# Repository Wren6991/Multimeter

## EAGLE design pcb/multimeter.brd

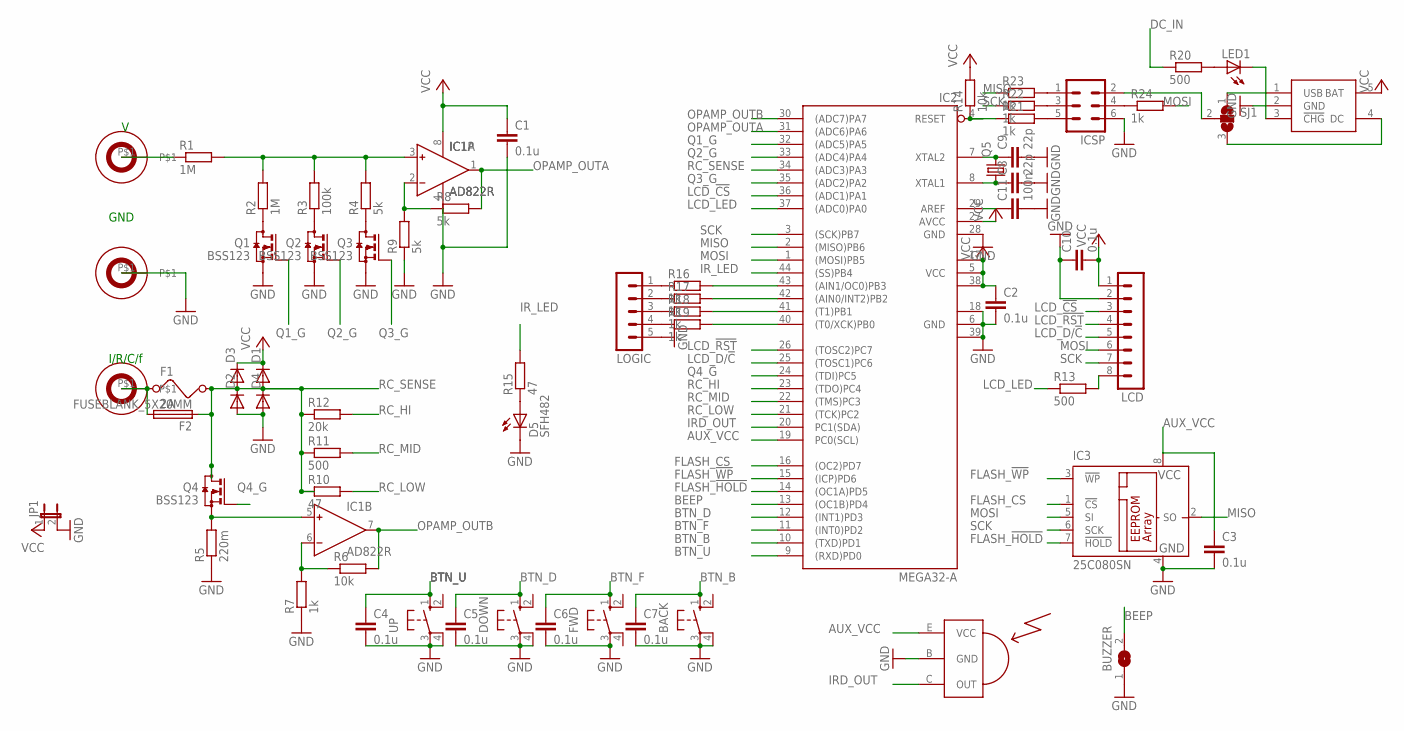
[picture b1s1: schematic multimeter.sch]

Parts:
BACK: 10-XX; B3F-10XX
BUZZER: SJW
C1, C2, C3, C4, C5, C6, C7, C10: 0.1u; C0805
C8, C9: 22p; C0603
C11: 100n; C0805
D1, D2, D3, D4: DIODE-SOD123; SOD123
D5: SFH482
DOWN: 10-XX; B3F-10XX
F1: 2A; R1206
F2: FUSEBLANK_5X20MM; FUSE_HOLDER_5X20MM
FWD: 10-XX; B3F-10XX
IC1: AD822R; SO8
IC2: MEGA32-A; TQFP44
IC3: 25C080SN; SO-08
ICSP: MA03-2
JP1: JP1E; JP1
LCD: MA08-1
LED1: LEDSML0805; SML0805
LOGIC: MA05-1
N$36: BINDINGPOST4MMPCB; BINDINGPOSTPCB
Q1, Q2, Q3, Q4: BSS123; SOT23
Q5: CRYSTALHC49UP; HC49UP
R1: 1M; 0207/12
R2: 1M; R0805
R3: 100k; R0805
R4, R8, R9: 5k; R0805
R5: 220m; R1206
R6, R14: 10k; R0805
R7, R16, R17, R18, R19, R21, R22, R23, R24: 1k; R0805
R10, R15: 47; R0805
R11, R13, R20: 500; R0805
R12: 20k; R0805
SJ1: SJ2W; SJ_2
U$1, U$2: BINDINGPOST4MMPCB; BINDINGPOSTPCB
U$3: IRDETECTOR; TO92-EBC
U$4: LITHIUMCHARGER; SOT23-5L
UP: 10-XX; B3F-10XX

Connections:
AUX_VCC: C3.1, IC2.19 (PC0(SCL)), IC3.8 (VCC), U$3.E (VCC)
BEEP: BUZZER.2, IC2.13 ((OC1B)PD4)
BTN_B: BACK.1 (S), C7.1, IC2.10 ((TXD)PD1)
BTN_D: C5.1, DOWN.1 (S), IC2.12 ((INT1)PD3)
BTN_F: C6.1, FWD.1 (S), IC2.11 ((INT0)PD2)
BTN_U: C4.1, IC2.9 ((RXD)PD0), UP.1 (S)
DC_IN: ICSP.2, R20.1, SJ1.2
FLASH_!HOLD: IC2.14 ((OC1A)PD5), IC3.7 (!HOLD)
FLASH_!WP: IC2.15 ((ICP)PD6), IC3.3 (!WP)
FLASH_CS: IC2.16 ((OC2)PD7), IC3.1 (!CS)
GND: BACK.3, BACK.4 (P1), BUZZER.1, C1.2, C2.2, C3.2, C4.2, C5.2, C6.2, C7.2, C8.2, C9.2, C10.1, C11.2, D2.A, D4.A, D5.K (C), DOWN.3, DOWN.4 (P1), FWD.3, IC1.4 (V-), IC2.6 (GND), IC2.18 (GND1), IC2.28 (GND), IC2.39 (GND2), IC3.4 (GND), ICSP.6, JP1.2, LCD.2, LOGIC.5, Q1.2 (S), Q2.2 (S), Q3.2 (S), R5.1, R7.1, R9.1, U$2.P$1, U$3.B (GND), U$4.2 (GND), UP.3, UP.4 (P1)
IRD_OUT: IC2.20 (PC1(SDA)), U$3.C (OUT)
IR_LED: IC2.44 ((SS)PB4), R15.2
LCD_!CS: IC2.36 ((ADC1)PA1), LCD.3
LCD_!RST: IC2.26 ((TOSC2)PC7), LCD.4
LCD_D/!C: IC2.25 ((TOSC1)PC6), LCD.5
LCD_LED: IC2.37 ((ADC0)PA0), R13.1
MISO: IC2.2 ((MISO)PB6), IC3.2 (SO), R23.1
MOSI: IC2.1 ((MOSI)PB5), IC3.5 (SI), LCD.6, R24.2
unnamed: D5.A, R15.1
unnamed: Q2.3 (D), R3.1
unnamed: LOGIC.1, R16.1
unnamed: IC1.3 (IN+), R1.2, R2.2, R3.2, R4.2
unnamed: IC1.5 (IN+), Q4.2 (S), R5.2
unnamed: LOGIC.2, R17.1
unnamed: IC1.6 (IN-), R6.1, R7.2
unnamed: LOGIC.3, R18.1
unnamed: IC1.2 (IN-), R8.1, R9.2
unnamed: LOGIC.4, R19.1
unnamed: IC2.43 ((AIN1/OC0)PB3), R16.2
unnamed: ICSP.4, R24.1
unnamed: IC2.42 ((AIN0/INT2)PB2), R17.2
unnamed: IC2.41 ((T1)PB1), R18.2
unnamed: IC2.40 ((T0/XCK)PB0), R19.2
unnamed: C9.1, IC2.7 (XTAL2), Q5.2
unnamed: R1.1, U$1.P$1
unnamed: C8.1, IC2.8 (XTAL1), Q5.1
unnamed: SJ1.3, U$4.4 (DC)
unnamed: IC2.4 (RESET), R14.1, R21.1
unnamed: SJ1.1, U$4.1 (USB)
unnamed: LED1.A, R20.2
unnamed: LED1.C, U$4.3 (!CHG)
unnamed: ICSP.5, R21.2
unnamed: ICSP.3, R22.2
unnamed: ICSP.1, R23.2
unnamed: C11.1, IC2.29 (AREF)
unnamed: LCD.8, R13.2
unnamed: F1.1, F2.2, N$36.P$1
unnamed: Q1.3 (D), R2.1
unnamed: Q3.3 (D), R4.1
OPAMP_OUTA: IC1.1 (OUT), IC2.31 ((ADC6)PA6), R8.2
OPAMP_OUTB: IC1.7 (OUT), IC2.30 ((ADC7)PA7), R6.2
Q1_G: IC2.32 ((ADC5)PA5), Q1.1 (G)
Q2_G: IC2.33 ((ADC4)PA4), Q2.1 (G)
Q3_G: IC2.35 ((ADC2)PA2), Q3.1 (G)
Q4_G: IC2.24 ((TDI)PC5), Q4.1 (G)
RC_HI: IC2.23 ((TDO)PC4), R12.2
RC_LOW: IC2.21 ((TCK)PC2), R10.2
RC_MID: IC2.22 ((TMS)PC3), R11.2
RC_SENSE: D1.A, D2.C, D3.A, D4.C, F1.2, F2.1, IC2.34 ((ADC3)PA3), Q4.3 (D), R10.1, R11.1, R12.1
SCK: IC2.3 ((SCK)PB7), IC3.6 (SCK), LCD.7, R22.1
VCC: C1.1, C2.1, C10.2, D1.C, D3.C, IC1.8 (V+), IC2.5 (VCC), IC2.17 (VCC1), IC2.27 (AVCC), IC2.38 (VCC2), JP1.1, LCD.1, R14.2, U$4.5 (BAT)

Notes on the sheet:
GND
I/R/C/f

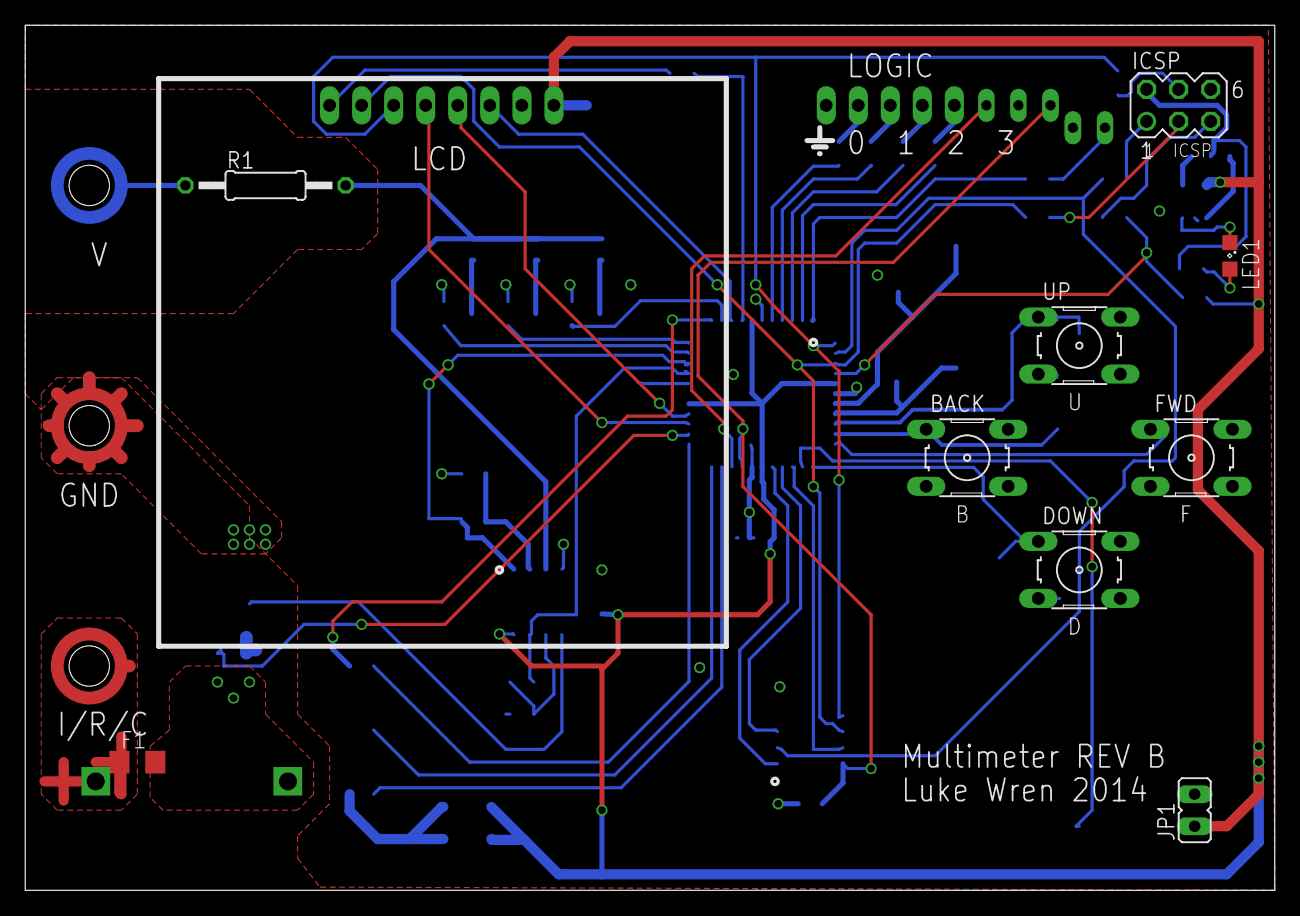
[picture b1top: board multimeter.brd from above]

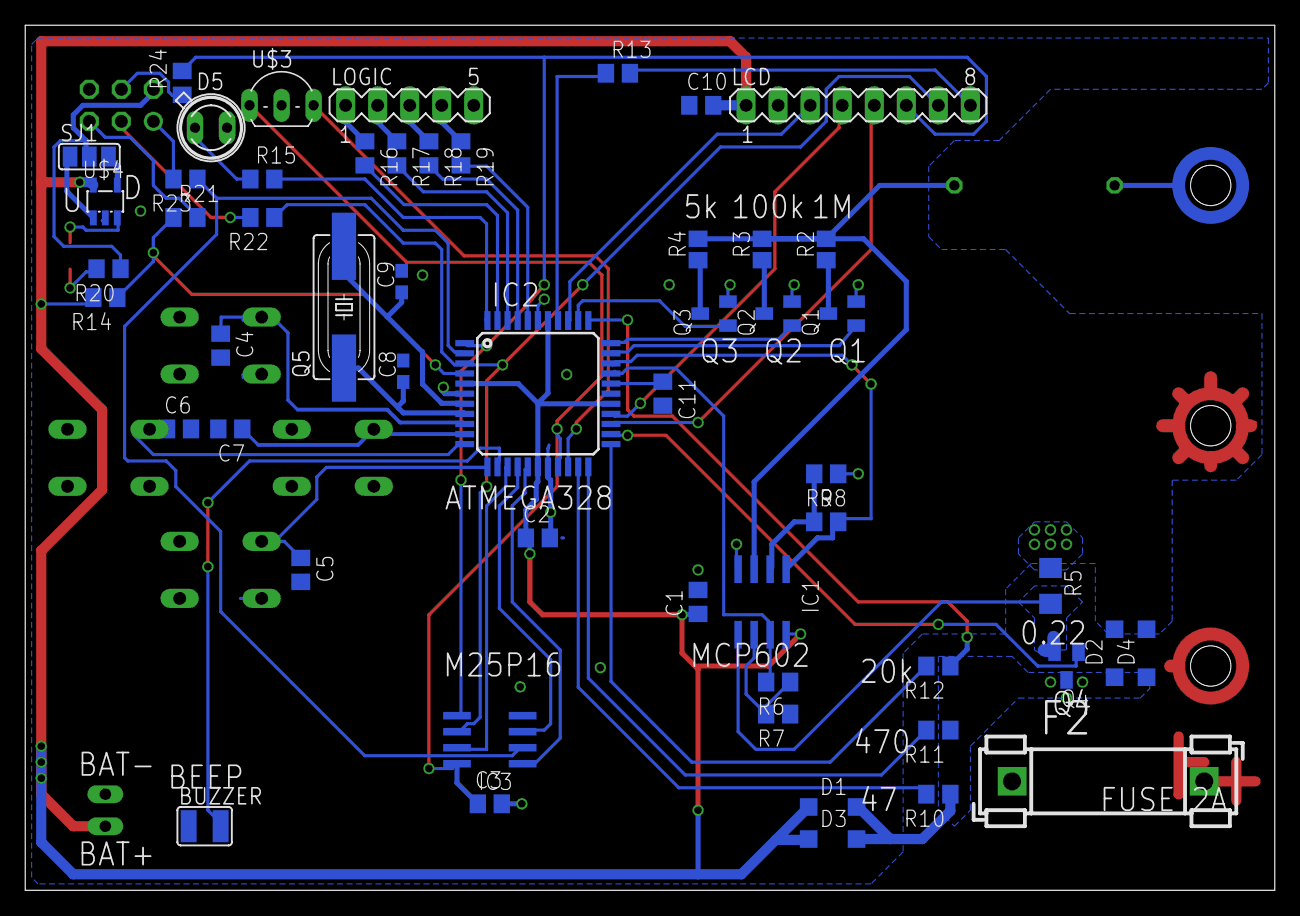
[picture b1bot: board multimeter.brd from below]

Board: 2 copper layers, 99.1 x 68.6 mm, 66 parts (55 on the bottom side), 62 nets.

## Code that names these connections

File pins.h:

#ifndef _PINS_H_
#define _PINS_H_

#define PORT_VATTEN PORTA
#define DDR_VATTEN DDRA
#define VATTEN_1M 0x20
#define VATTEN_100k 0x10
#define VATTEN_5k 0x04
#define VATTEN_ALL (VATTEN_1M | VATTEN_100k | VATTEN_5k)

#define DDR_IGATE DDRC
#define PORT_IGATE PORTC
#define IGATE 0x20
#define CURRENT_ON true
#define CURRENT_OFF false

#define PORT_RC PORTC
#define DDR_RC DDRC
#define RC_HI 0x10
#define RC_MID 0x08
#define RC_LOW 0x04

#define PORT_RCSENSE PORTA
#define DDR_RCSENSE DDRA
#define PIN_RCSENSE PINA
#define RC_SENSE 0x08

#define VIN_V 6
#define VIN_I 7
#define VIN_RC 3
#define VIN_BANDGAP 0x1e

#endif // _PINS_H_

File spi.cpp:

#include "spi.h"

#define LCD_CS 0x02
#define PORT_LCD_CS PORTA
#define DDR_LCD_CS DDRA
#define FLASH_CS 0x80
#define FLASH_WP 0x40
#define FLASH_HOLD 0x20
#define PORT_FLASH_CS PORTD
#define DDR_FLASH_CS DDRD

#define PORT_SPI PORTB
#define DDR_SPI DDRB
#define SPI_MOSI 0x20
#define SPI_MISO 0x40
#define SPI_SCK 0x80
#define SPI_SS 0x10
#define SPI_ALL (SPI_MOSI | SPI_MISO | SPI_SCK | SPI_SS)

void spi_init()
{
    spi_deassert();
    DDR_SPI = (DDR_SPI & ~SPI_ALL) | (SPI_MOSI | SPI_SCK | SPI_SS);
    SPCR0 = 0x50;    // no interrupt, SPI enabled, MSB first, master, divide clock by four (on top of four phases)
    SPSR0 = 0x01;    // SPI2X enabled (gives effective SPI clock of FCPU/8 = 1MHz)
}

void spi_deassert()
{
    //DDR_LCD_CS &= ~LCD_CS;
    PORT_LCD_CS |= LCD_CS;
    //DDR_FLASH_CS &= ~FLASH_CS;
    PORT_FLASH_CS |= FLASH_CS;
}

void spi_assert(uint8_t device)
{
    switch (device)
    {
    case spi_assert_flash:
        PORT_FLASH_CS = (PORT_FLASH_CS & ~FLASH_CS) | FLASH_HOLD;
        DDR_FLASH_CS |= FLASH_CS | FLASH_HOLD;
        break;
    case spi_assert_lcd:
        PORT_LCD_CS &= ~LCD_CS;
        DDR_LCD_CS |= LCD_CS;
        break;
    }
}

void spi_send_byte(uint8_t x)
{
    SPDR0 = x;
    while (!(SPSR0 & 0x80));
}

void spi_send(uint8_t *message, uint8_t length)
{
    while (length--)
        spi_send_byte(*message++);
}

void spi_receive();

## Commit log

2014-09-06 Added simple SPI functions
2014-09-06 added SPI files
2014-09-06 added PCB files
2014-09-06 added pcb files, connected charge LED to DC input instead of battery, connected Flash VCC to same net as IRD VCC
2014-10-02 added 8448 screen support, font files
2014-10-02 added assembly files for logic capture + scope
